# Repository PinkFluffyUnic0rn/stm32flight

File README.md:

STM32 Flight controller
=========================

DIY quadcopter flight controller from scratch, two boards and software.

[Project structure](https://github.com/PinkFluffyUnic0rn/stm32flight/wiki/Project-structure) 
is described on wiki page.

Software
=======

Software part implements all basic quadcopter flight control features.
Configuration commands and settings are on
[wiki page](https://github.com/PinkFluffyUnic0rn/stm32flight/wiki/FC-configuration-commands-and-settings).

* Rotation speed stabilization using gyroscope readings.
* Attitude stabilization using accelerometer/gyroscope readings.
* Yaw stabilization using gyroscope readings.
* Yaw stabilization using magnetometer/gyroscope readings.
* Acceleration stabilization using accelerometer readings.
* Altitude stabilization using barometer/accelerometer readings.
* Position stabilization using GNSS/accelerometer/magnetometer readings.
* Configuration through Wi-Fi.
* Dshot-300 and Dshot-600 ESC control protocols.
* IRC Tramp VTX control.
* OSD for digital VTX through MSP.
* Telemetry and control through eLRS.
* Terminal configuration tool.
* Qt5 based GUI configuration tool for desktop and android.

STM32H723 based board
=======
[Schematic](https://github.com/PinkFluffyUnic0rn/stm32flight/blob/main/pcb/H7/schematic.pdf)

 * MCU: STM32H723VGT6
 * Crystall oscillator: 20 Mhz
 * DC-DC converter for control board: TPS5430
 * Control board voltage regulator: LDL1117S33R
 * Accelerometer/Gyroscope: ICM-42688-P
 * Barometer: DPS368
 * Magnetometer: LIS3MDL
 * External magnetometer: MMC5983MA
 * Flight log storage: W25Q
 * GNSS module: M10
 * Remote control: ERLS CRSF receiver
 * Telemetry/debug/config: ESP8285

STM32F405 based board
=======
 * MCU: STM32F405RGT6
 * Crystall oscillator: 20 Mhz
 * DC-DC converter for control board: TPS5430 (external)
 * Control board voltage regulator: LDL1117S33R-3.3
 * Accelerometer/Gyroscope: ICM-42688-P
 * Barometer: DPS368
 * Magnetometer: QMC5883L
 * Flight log storage: W25Q
 * GNSS module: M10
 * Remote control: ERLS CRSF receiver
 * Telemetry/debug/config: ESP8285

The quadcopter used for testing
==========
 * Motors: 1404, 3800 kV
 * Props: 3030
 * Battery: 14.8v (4s), 1300 mAh, 120c
 * Frame: carbon fiber
 * Canopy, VTX mount: 3d printed PLA
 * Landing pads: EVA foam

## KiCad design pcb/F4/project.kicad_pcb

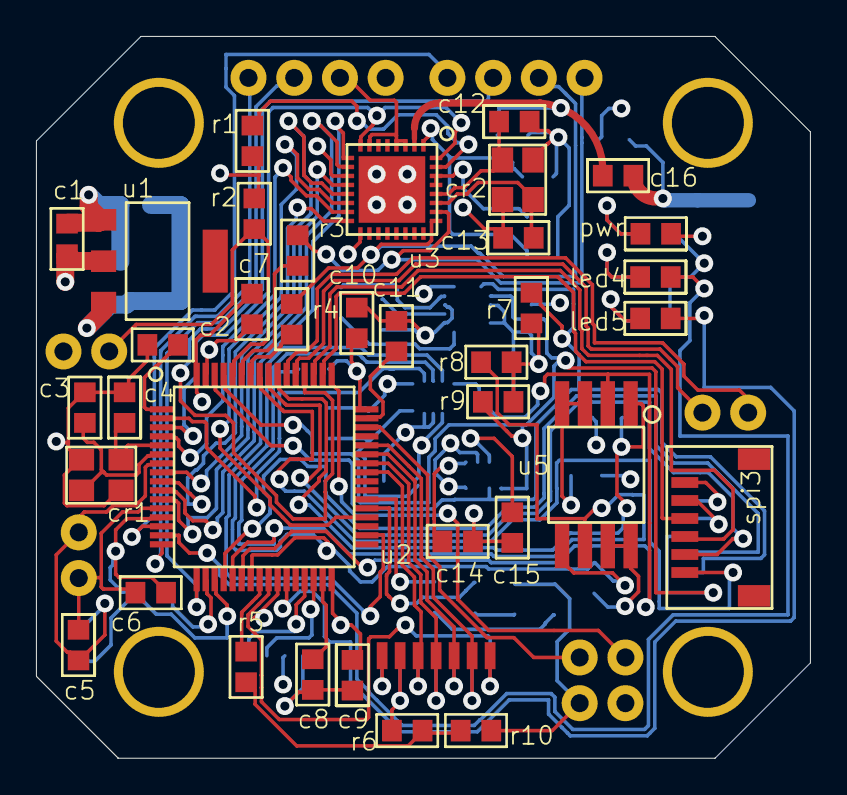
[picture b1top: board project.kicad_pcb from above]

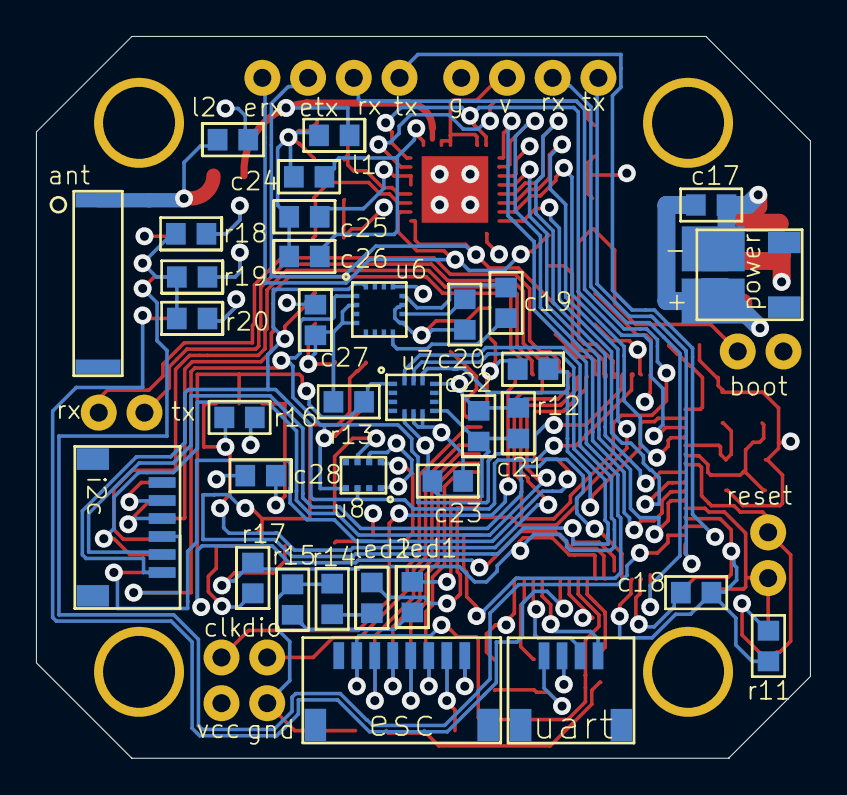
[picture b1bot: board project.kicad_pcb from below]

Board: 4 copper layers, 43.0 x 40.1 mm, 70 parts (34 on the bottom side), 45 nets.

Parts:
ant: Comment; rainsun antenna
c1: Comment; PCBComponent_1
c2, c3, c4, c5, c6, c7, c8, c9, c10, c11, c12, c13, c14, c15, c16, c17, c18, c19, c20, c21, c22, c23, c24, c25, c26, c27, c28: Comment; 0603
cr1, cr2: Comment; smd_crystall
esc: Comment; SH1.0-8
i2c: Comment; SH1.0-6
l1, l2: Comment; 0603
led1, led2, led4, led5: Comment; 0603
power: Comment; sh1.0-2
pwr: Comment; 0603
r1, r2, r3, r4, r5, r6, r7, r8, r9, r10, r11, r12, r13, r14, r15, r16, r17, r18, r19, r20: Comment; 0603
spi3: Comment; SH1.0-6
u1: Comment; ams1117
u2: Comment; lqfp64
u3: Comment; esp8285
u5: Comment; w25q
u6: Comment; qmc5883l
u7: Comment; icm42688
u8: Comment; DPS368
uart: Comment; sh1.0-4

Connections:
ant: ant.6, c16.1, l2.1
antcap: c16.1, l1.1, u3.4
boot: r2.1, u2.1
ch1: esc.1, u2.1
ch2: esc.1, u2.1
ch3: esc.1, u2.1
ch4: esc.1, u2.1
ch5: spi3.1, u2.1
ch6: spi3.1, u2.1
cs1: r12.1, u2.1, u7.1
cs2: r16.1, u2.1, u5.1
cs4: u2.1, u3.4
current: esc.1, u2.1
esp_rx: r3.1, u3.4
esp_tx: r4.1, u3.4
espboot: u2.1, u3.4
ext_rstb: u2.1, u3.4
exti1: u2.1, u3.4
gnd: c1.1, c2.1, c3.1, c4.1, c5.1, c6.1, c7.1, c8.1, c9.1, c10.1, c11.1, c12.1, c13.1, c14.1, c15.1, c17.1, c18.1, c20.1, c21.1, c22.1, c23.1, c24.1, c25.1, c26.1, c27.1, c28.1, cr1.3, cr2.3, esc.1, i2c.1, l1.1, l2.1, power.1, r1.1, r2.1, r10.1, r14.1, r15.1, r18.1, r19.1, r20.1, spi3.1, u1.1, u2.1, u5.1, u6.1, u7.1, u8.1, uart.1
led1: led2.1, u2.1
led1r: led2.1, r14.1
led2: led1.1, u2.1
led2r: led1.1, r15.1
led3r: pwr.1, r18.1
led4: led4.1, u2.1
led4r: led4.1, r19.1
led5: led5.1, u2.1
led5r: led5.1, r20.1
miso: r13.1, u2.1, u5.1, u7.1
miso2: u2.1, u3.4
mosi: r17.1, u2.1, u5.1, u7.1
mosi2: u2.1, u3.4
nrst: c5.1, r11.1, u2.1
osc_in: c4.1, cr1.3, u2.1
osc_out: c3.1, cr1.3, u2.1
pa4: i2c.1, u2.1
pa15: spi3.1, u2.1
pb15: u2.1, u3.4
pc10: spi3.1, u2.1
qmc_c1: c20.1, u6.1
qmc_setc: c19.1, u6.1
qmc_setp: c19.1, u6.1
res12k: r1.1, u3.4
rx1: r3.1, u2.1
rx3: u2.1, uart.1
sck: r8.1, u2.1, u5.1, u7.1
sck2: u2.1, u3.4
scl: i2c.1, r9.1, u2.1, u6.1, u8.1
sda: i2c.1, r7.1, u2.1, u6.1, u8.1
tx1: r4.1, u2.1
tx3: u2.1, uart.1
v2_1: r5.1, r6.1, r10.1
v2_2: r5.1, u2.1
vbat: c2.1, u2.1
vcap1: c8.1, u2.1
vcap2: c11.1, u2.1
vcc: c1.1, c6.1, c7.1, c9.1, c10.1, c14.1, c15.1, c18.1, c21.1, c22.1, c23.1, c24.1, c25.1, c26.1, c27.1, c28.1, i2c.1, pwr.1, r7.1, r8.1, r9.1, r11.1, r12.1, r13.1, r16.1, r17.1, spi3.1, u1.1, u2.1, u3.4, u5.1, u6.1, u7.1, u8.1, uart.1
vesc: esc.1, r6.1
vin: c17.1, power.1, u1.1
xtal_in: c12.1, cr2.3, u3.4
xtal_out: c13.1, cr2.3, u3.4

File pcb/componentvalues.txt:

c1	4.7 uF
c2	0.1 uF
c3	18 pF
c4	18 pF
c5	0.1 uF
c6	0.01 uF
c7	0.1 uF
c8	2.2 uF
c9	0.1 uF
c10	0.1 uF
c11	2.2 uF
c12	18 pF
c13	18 pF
c14	0.1 uF
c15	0.1 uF
c16	5.6 pF
c17	1 uF
c18	0.1 uF
c19	0.22 uF
c20	4.7 uF
c21	2.2 uF
c22	0.1 uF
c23	0.01 uF
c24	0.01 uF
c25	0.1 uF
c26	1 uF
c27	0.1 uF
c28	0.1 uF

r1	12k
r2	10k
r3	-
r4	-
r5	0 Ohm
r6	3k
r7	10k
r8	10k
r9	10k
r10	680 Ohm
r11	10k
r12	10k
r13	10k
r14	1k
r15	1k
r16	10k
r17	10k
r18	1k
r19	1k
r20	1k

l1	-
l2	-

cr1	20 mHz
cr2	40 mHz
led1	orange led
led2	blue led
pwr	green led
led4	yellow led
led5	red led

u1	LDL1117S33R
u2	STM32F405RGT6
u3	ESP8285
u4	DPS368
u5	W25Q128FVSIG
u6	QMC5883L
u7	ICM-42688-P

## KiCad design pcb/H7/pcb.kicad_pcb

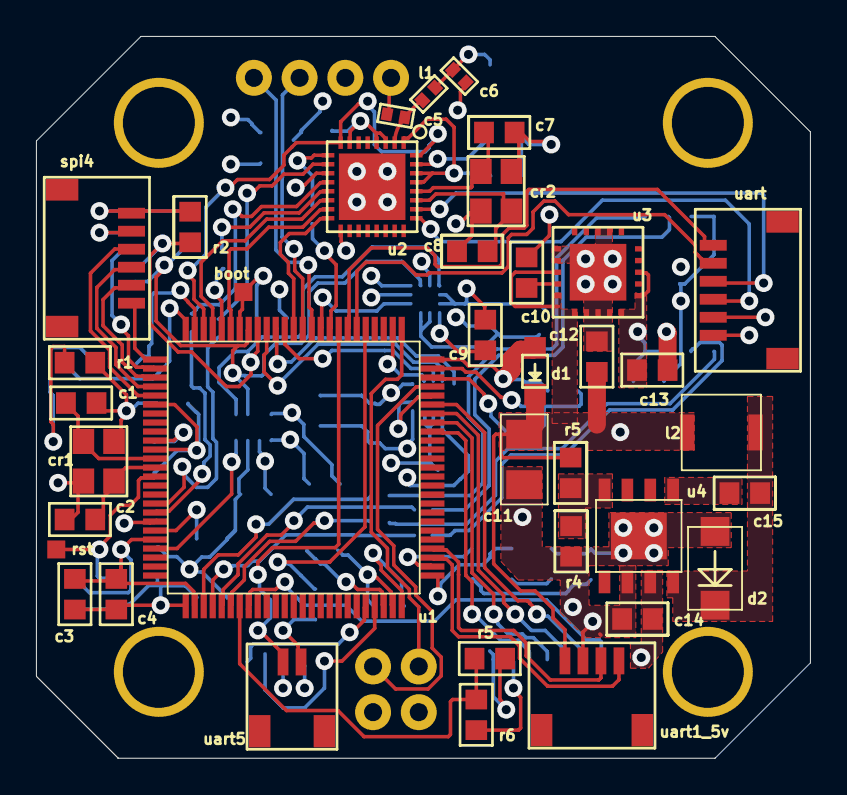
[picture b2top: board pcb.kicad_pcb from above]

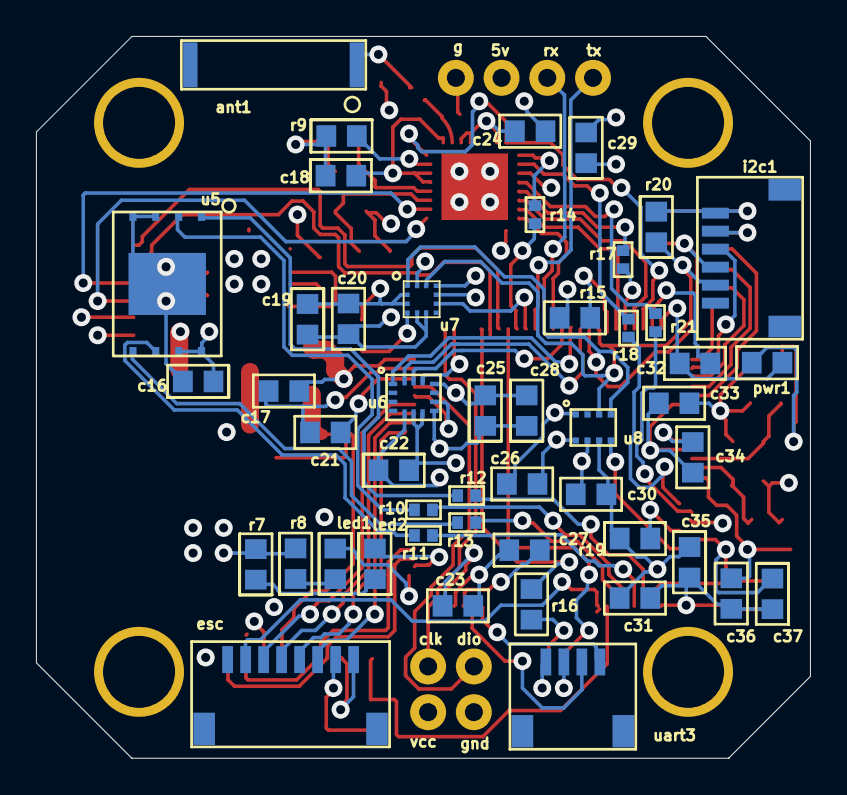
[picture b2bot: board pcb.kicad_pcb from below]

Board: 4 copper layers, 43.0 x 40.1 mm, 83 parts (48 on the bottom side), 59 nets.

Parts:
ant1: AN9520; rainsun antenna
c1, c2, c7, c8: 18 pF; 0603
c3, c10, c18, c20, c35: 1 uF; 0603
c4, c9, c16, c17, c19, c23, c24, c25, c26, c30, c31, c32, c33, c34, c36, c37: 0.1 uF; 0603
c5, c6: tbd; 0402
c11: 100 uF; 1206
c12, c14, c29: 10 uF; 0603
c13: 47 uF; 0603
c15, c22: 0.01 uF; 0603
c21, c27, c28: 2.2 uF; 0603
cr1: 20 Mhz; smd_crystall
cr2: 40 Mhz; smd_crystall
d1: Comment; SOD-323
d2: SS34
esc: JST SH-8; SH1.0-8
i2c1: JST SH-6; SH1.0-6
l1: tdb; 0402
l2: 10 uH; inductor
led1: blue LED; 0603
led2: orange LED; 0603
pwr1: green LED; 0603
r1, r7, r8: 1 kOhm; 0603
r2, r20: 3 kOhm; 0603
r4: 3.3 kOhm; 0603
r5: 680 Ohm; 0603
r5#2, r15: 10 kOhm; 0603
r6: 5.1 kOhm; 0603
r9: 12 kOhm; 0603
r10, r11, r12, r13, r14, r17, r18, r21: 33 Ohm; 0402
r16: 100 Ohm; 0603
r19: 47 Ohm; 0603
spi4: JST SH-6; SH1.0-6
u1: STMH723VGT6; lqfp100
u2: ESP8285; esp8285
u3: TPS7A4700; TPS7A470
u4: TPS5430DDAR; tps5430
u5: Comment; W25N
u6: ICM-42688-P; icm42688
u7: LIS3MDLTR; lis3mdl
u8: DPS368XTSA1; DPS368
uart: JST SH-6; SH1.0-6
uart1_5v, uart3: JST SH-4; sh1.0-4
uart5: JST SH-2; sh1.0-2

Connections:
ant: ant1.6, c6.1, l1.1
antcap: c5.1, l1.1, u2.4
boot: r15.1, u1.1
ch1: esc.1, u1.1
ch2: esc.1, u1.1
ch3: esc.1, u1.1
ch4: esc.1, u1.1
current: esc.1, u1.1
dcdc_boot: c15.1, u4.9
drdy: u1.1, u7.6
esp_rx: u2.4, uart.1
esp_tx: u2.4, uart.1
espboot: u1.1, u2.4
ext_rstb: u1.1, u2.4
exti1: u1.1, u2.4
fsync: u1.1, u6.1
gnd: c1.1, c2.1, c3.1, c4.1, c5.1, c6.1, c7.1, c8.1, c9.1, c10.1, c11.10, c12.1, c13.1, c14.1, c16.1, c17.1, c18.1, c19.1, c20.1, c21.1, c22.1, c23.1, c24.1, c25.1, c26.1, c27.1, c28.1, c29.1, c30.1, c31.1, c32.1, c33.1, c34.1, c35.1, c36.1, c37.1, cr1.3, cr2.3, d2.8, esc.1, i2c1.1, r1.1, r4.1, r5.1, r7.1, r8.1, r9.1, r15.1, spi4.1, u1.1, u3.9, u3.10, u4.9, u5.11, u5.12, u6.1, u7.6, u8.1, uart.1, uart1_5v.1, uart3.1
led1: led1.1, u1.1
led1r: led1.1, r8.1
led2: led2.1, u1.1
led2r: led2.1, r7.1
lis_c1: c9.1, u7.6
loop: c15.1, d2.8, l2.7, u4.9
miso1_1: r10.1, u1.1
miso1_2: r10.1, u5.12
miso2_1: r18.1, u1.1
miso2_2: r18.1, u2.4
miso3: u1.1, u6.1
miso4: spi4.1, u1.1
mosi1_1: r13.1, u1.1
mosi1_2: r13.1, u5.12
mosi2_1: r21.1, u1.1
mosi2_2: r21.1, u2.4
mosi3: u1.1, u6.1
mosi4: spi4.1, u1.1
nr: c10.1, u3.9
nrst: c36.1, u1.1
nss1_1: r12.1, u1.1
nss1_2: r12.1, u5.12
nss2_1: r17.1, u1.1
nss2_2: r17.1, u2.4
nss3: u1.1, u6.1
nss4: spi4.1, u1.1
osc_in: c1.1, cr1.3, u1.1
osc_out: c2.1, cr1.3, u1.1
pe0: u1.1, u2.4
pe3: i2c1.1, u1.1
pwrled: pwr1.1, r1.1
res12k: r9.1, u2.4
rx1: u1.1, uart1_5v.1
rx3: u1.1, uart3.1
rx4: u1.1, uart.1
rx5: u1.1, uart5.1
sck1_1: r11.1, u1.1
sck1_2: r11.1, u5.12
sck2_1: r14.1, u1.1
sck2_2: r14.1, u2.4
sck3: u1.1, u6.1
sck4: spi4.1, u1.1
scl: i2c1.1, r2.1, u1.1, u7.6, u8.1
sda: i2c1.1, r20.1, u1.1, u7.6, u8.1
sdo: u1.1, u8.1
sence: r4.1, r5#2.1, u4.9
tx1: u1.1, uart1_5v.1
tx3: u1.1, uart3.1
tx4: u1.1, uart.1
tx5_1: r16.1, u1.1
tx5_2: r16.1, uart5.1
v5: c11.10, c12.1, d1.4, l2.7, r5#2.1, u3.9, uart1_5v.1
v_bat: r5.1, r6.1, u1.1
vcap1: c21.1, u1.1
vcap2: c27.1, u1.1
vcc: c3.1, c4.1, c13.1, c16.1, c17.1, c18.1, c19.1, c20.1, c22.1, c23.1, c24.1, c25.1, c26.1, c28.1, c29.1, c30.1, c31.1, c32.1, c33.1, c34.1, c35.1, c37.1, d1.4, i2c1.1, pwr1.1, r2.1, r19.1, r20.1, spi4.1, u1.1, u2.4, u3.9, u5.12, u6.1, u7.6, u8.1, uart.1, uart3.1
vin: c14.1, esc.1, r6.1, u4.9
vref+: r19.1, u1.1
xtal_in: c7.1, cr2.3, u2.4
xtal_out: c8.1, cr2.3, u2.4

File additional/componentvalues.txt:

main board:
c1	0.1 uF
c2	0.1 uF
c3	18 pF
c4	18 pF
c5	0.1 uF
c6	0.1 uF
c9	0.1 uF
c11	2.2 uF
c12	0.1 uF
c13	0.1 uF
c14	2.2 uF
c15	5.6 pF
l1	18 pF
c16	18 pF
c17	0.1 uF
c18	10 uF
c19	0.1 uF
c20	0.22 uF
c21	4.7 uF
c22	0.1 uF
c23	2.2 uF
c24	0.01 uF
c26	0.1 uF
c27	0.1 uF
c28	0.1 uF
c29	0.1 uF
c31	0.1 uF

c7	12 kOhm
c8	0 Ohm
c30	10 kOhm
c10	0 Ohm
r1	10k
r2	3 kOhm
r3	10 kOhm
r4	3 kOhm
r5	10 kOhm
r6	10 kOhm
r7	1k
r8	1k
r9	10k
r10	10k

c25	mH
l2	mH

led1:	orange led
led2:	blue led
u1:	AMS1117-3.3
u2:	STM32F405RGT6
u3:	ESP8285
u4:	HP206C
u5:	W25Q128FVSIG
u6:	ICM-42688-P
u7:	QMC5883L

dc-dc converter:
l1:	10 uH
r1:	10 kOhm
r2:	3.3 kOhm
r3:	4.7 kOhm
r4:	27 kOhm
c1:	0.1 uF
c2:	10 uF
c3:	100 uF
u1:	tps5430

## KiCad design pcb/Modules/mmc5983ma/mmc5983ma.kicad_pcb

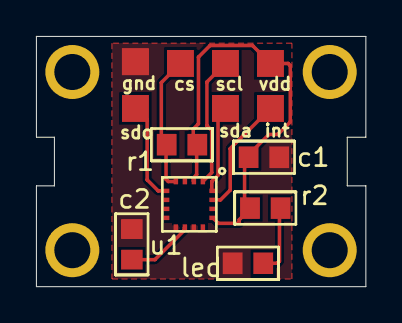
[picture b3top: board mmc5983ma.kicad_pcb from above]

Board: 2 copper layers, 18.3 x 13.9 mm, 6 parts (0 on the bottom side), 5 nets.

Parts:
c1, c2: Comment; 0603
led: Comment; 0603
r1, r2: Comment; 0603
u1: Comment; qmc5883l

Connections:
cap: c2.1, u1.1
cs: r1.1, u1.1
gnd: c1.1, c2.1, led.1, u1.1
led: led.1, r2.1
vcc: c1.1, r1.1, r2.1, u1.1

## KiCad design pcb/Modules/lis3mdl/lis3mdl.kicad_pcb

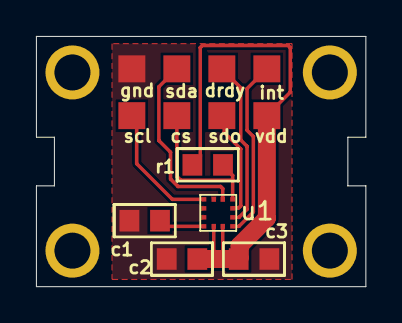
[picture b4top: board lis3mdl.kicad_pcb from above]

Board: 2 copper layers, 18.3 x 13.9 mm, 5 parts (0 on the bottom side), 4 nets.

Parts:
c1, c2, c3: Comment; 0603
r1: Comment; 0603
u1: Comment; lis3mdl

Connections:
c1: c1.1, u1.6
cs: r1.1, u1.6
gnd: c1.1, c2.1, c3.1, u1.6
vdd: c2.1, c3.1, r1.1, u1.6

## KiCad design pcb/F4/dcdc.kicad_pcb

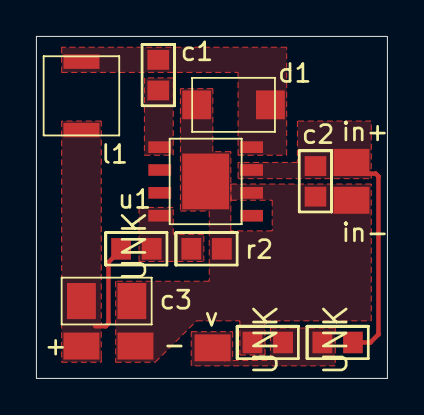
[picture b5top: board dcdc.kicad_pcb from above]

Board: 2 copper layers, 19.5 x 19.0 mm, 10 parts (0 on the bottom side), 7 nets.

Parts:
UNK: Comment; 0603
UNK#2, UNK#3: Comment; 0603
c1, c2: Comment; 0603
c3: Comment; 1206
d1: Comment; SS34
l1: Comment; inductor
r2: Comment; 0603
u1: Comment; tps5430

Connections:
boot: c1.1, u1.9
gnd: UNK#3.1, c2.1, c3.10, d1.8, r2.1, u1.9
in: UNK.1, c2.1, u1.9
loop: c1.1, d1.8, l1.7, u1.9
out: UNK#2.1, c3.10, l1.7
sense: UNK#2.1, r2.1, u1.9
v: UNK.1, UNK#3.1

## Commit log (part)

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2024-10-30 circuit updated
2024-10-30 dc-dc circuit added
2024-10-30 dc-dc circuit fix
2024-10-30 dc-dc converted info updated
2024-11-03 Debug conenction is now made by AP created by copter
2024-11-03 README.md changed
2024-11-03 README.md fixed
2024-11-08 README updated
2024-11-14 yaw control is now performed by left joystick
2024-11-14 wifi timeut removed, wifi control commands removed
2024-11-14 rc cleanup
2024-11-16 README.md update
2024-11-19 Some main.c comments added
2024-11-19 main.c comments updated
2024-11-20 dsp comments updated
2024-11-20 README.md update, comments update
2024-11-23 trying to add climb with constant rate by barometer
2024-11-23 trying to use barometer
2024-11-24 altitude reset from elrs
2024-11-24 arming indication and error leds added
2024-11-26 onboard flash activated
2024-11-26 trying to estimate climb rate from accelerometer
2024-12-02 trying to make constant climb speed
2024-12-02 config change
2024-12-05 gyro calibration on start removed
2024-12-05 tilt is now limited with 45 degrees instead of 30
2024-12-05 some cleanup, comments updated
2024-12-23 switched to new board, with mpu6500
2025-02-23 Starting without esp8266 restart
2025-02-25 Tried to fix baudrate on-run change for esp8266, removed hardcoded mpu6500 offsets
2025-02-25 SPI baudrate divider set to 4, some cleanup
2025-02-25 flash log fixes, log set size commands added
2025-02-26 add new values to log
2025-02-26 event timer remain added
2025-02-26 using remain to adjust frequency
2025-02-27 fixed w25q timeouts, esp8266 baudrate slowed
2025-02-28 esp8266 memmove removed from callback
2025-03-01 PLL multiplier increased, enqueqe function for ESP8266 fifo removed
2025-03-06 GNSS added
2025-03-08 ESP8266 switched to same interface as other devices
2025-03-08 debug commands refactored
2025-03-09 Device status command added
2025-03-09 Added comment
2025-03-09 Telemetry fixes and refactoring
2025-03-10 altitude telemetry fix
2025-03-17 vertical speed calculation by vector projection added
2025-03-17 altitude complimentary filter added
2025-03-20 MPU6500 dlpf changes
2025-03-22 Yaw complimentary filter added to merge magnetometer heading and gyro z axis
2025-03-22 Create LICENSE
2025-03-23 Some naming fixes
2025-03-23 Motor thrust adjust added
2025-04-08 Switched to stm32f405 and ICM42688
2025-04-08 README fixed
2025-04-11 motors changed
2025-04-17 values changed; unused values list deleted
2025-04-17 values updated
2025-04-17 more accurate weights measured
2025-04-17 compopnent values updated
2025-04-20 comment removed
2025-04-21 switched to multishot
2025-05-05 switched to new board with esp connected through SPI
2025-05-05 esp32 code added
2025-05-05 values changed
2025-05-06 Board changed
2025-05-08 switched to all-in-one esc, pid frequency set to 4k
2025-05-08 README changed
2025-05-09 pitch correction removed
2025-05-14 Fixing wifi connection for high speed upload
2025-05-15 Reworking confuration commands protocol
2025-05-16 trying to speed up spi
2025-05-16 changed UDP packet size
2025-05-18 trying to get better spi transmition speed
2025-05-19 log transmition protocol enhanced
2025-05-20 small README error fixed
2025-05-20 spaces removed, uavconf comments added
2025-05-20 sub microsecond delays added
2025-05-20 util comments added
2025-05-21 log record size changed
2025-05-21 maximum thrust value added
2025-05-22 spi speed lowered
2025-05-22 write only mode for w25q added
2025-05-22 emergency disarm when upside down, ESP SPI CRC check disabled
2025-05-23 disabled magnetometer check, values adjusted
2025-05-23 README.md updated with log documentation
2025-05-23 switched to CRC-16 for controll comamnds and log records, stm32 periphery initialization moved to separate file
2025-05-24 PT1 filter added
2025-05-24 trying to fix drifting
2025-05-29 esp8266 bugfixes, acro mode returned
2025-06-01 magnetometer OSR increased
2025-06-05 gyro lpf added, PID values changed
2025-06-06 D term filtering added
2025-06-07 pid changes
2025-06-09 voltage monitoring added
2025-06-09 pcb directory renamed
2025-06-09 battery monitoring divider changed, battery monitor lpf added
2025-06-09 component values updated
2025-06-12 config generation gui tool added
2025-06-12 working on config gui
2025-06-12 commands added to gui widgets
2025-06-13 commands parsing to common structure added
2025-06-14 Info tab added
2025-06-14 hotkeys added`
2025-06-14 classes refactoring
2025-06-17 uav command check fixed
2025-06-24 terminal uavconf connected to same API
2025-06-24 directory structure changed
2025-06-24 uavconf directory structure reworking
2025-06-28 frame changed, crsf channels enum added
2025-07-03 swtiched to dshot
2025-07-03 dshot cosmetic changes
2025-07-04 README updated, dshot comments added
2025-07-06 delays changed, ESCs configuration added
2025-07-10 partial setting send added, trying to altitude hold make stabilize when moving
2025-07-13 PID tuning for 2s battery set using Ziegler-Nichols method, I-term computing disabled disarmed
2025-07-15 No I-term when no throttle
2025-07-16 trying to setup thrust PIDs
2025-07-27 log field mapping fixes
2025-07-27 log writing fixes
2025-07-28 working on log guia config
2025-07-29 working on log config
2025-07-29 unique record field indexes in gui added
2025-07-31 log writing fix for maximum records count, w25 timeouts bugfix, stm32 systick to float seconds utility function added
2025-07-31 Log functions and settings moved to separate files
2025-08-01 log downloading cmd priniting to terminal added, get log record command timeout increased
2025-08-06 pcb updated, sensor adjustments changed
2025-08-10 4s pid values adjusted
2025-09-08 switching to dps368, working on stable altitude hold
2025-09-10 trying to work with hover throttle
2025-09-10 new pcb added
2025-09-12 stabilized around hover throttle acceleration mode added, altitude hold around hover throttle added
2025-09-14 hover throttle tilt compensation fixed
2025-09-15 clear i term when zero throttle
2025-10-01 hover throttle tilt compensation changed
2025-10-05 This is BOM
    You can edit it according to your region but I have used mostly internationally available parts.
2025-10-05 This is CPL file
    I haven't referenced it at all, I will complete it later as I don't have time right now. All the footprints are same as given in Gerber files.
2025-10-14 althold fixes
2025-10-18 git accelerometer offset added
2025-11-06 i2c and uart tx processed through DMA, bilinear PID implementaion added
2025-11-06 trying to switch to bilinear transform derived PID
2025-11-08 bilinear transform derived PID I-term clamp and I-term reset added
2025-11-09 Doxygen for dsp.h added
2025-11-09 I-term limit adjusted
2025-11-09 Command, CRC, global and log doxygen added
2025-11-10 main.c doxygen added
2025-11-10 logging event enabled, set_pid return codes fixed
2025-11-10 cosmetic changes
2025-12-10 trying to fight altitude drop, custom log values added
2025-12-16 magnetometer thrust calibration added
2025-12-17 config commands, dshot and running values moved to separate files
2025-12-17 magnetometer calibrated better
2025-12-18 error accumulation when disarmed is fixed
2026-01-03 autopilot activation flag protection
2026-01-04 autopilot yaw added
2026-01-05 adding autopilot settings
2026-01-05 zero autopilot track points protection
2026-01-12 PCB added
2026-01-12 filters and pid controllers grouped into arrays
2026-01-13 Setting switched to nested structure
2026-01-13 global variable names now start with capital letters, magnetometer offset applied immideately
2026-01-13 tscale fixed
2026-01-14 roll, pitch, yaw offsets now calculated once, circular PID how using bilinear transform
2026-01-14 Separaty apply command added
2026-01-15 unified set command for all settings added
2026-02-02 DShot moved to separate device
2026-02-07 periphery initialization reworked
2026-02-08 added periphconf
2026-02-15 devices initialization reworked
2026-02-15 Log analyzing scripts pushed
2026-02-16 makefile reworked, stm32h7 hal added
2026-02-17 working on stm32h7 support
2026-02-20 trying to fix dshot for H7
2026-02-20 fixing adc for H7
2026-02-21 debug uart interrupt fixed
2026-02-22 trying to fix dshot issue on H7
2026-02-23 upadted readme
2026-02-24 Kicad project added for H7
2026-02-24 README.md updated again
2026-02-24 schematic updated
2026-02-24 schematic source updated
2026-02-24 pcb update
2026-02-24 F4 pcb updated
2026-02-24 schematic added to readme
2026-02-25 small comment fix
2026-02-25 schematic fix
2026-02-26 trying to fix dshot issue with high frequency timer, schematic numbers fix
2026-02-28 trying to fix dshot issue
2026-03-07 schematic upadted
2026-03-07 irc vtx inittialization fix
2026-03-07 irc fix
2026-03-09 current sence fix
2026-03-09 working on magnetometer calibration script
2026-03-10 battery sensor scaling added, i term scaling for dual loop pid mode added, configs updated
2026-03-10 adc sampling time changed
2026-03-10 adjusting adc
2026-03-10 calibration order change
2026-03-10 magnetometer config update for h7
2026-03-11 scheduler time measurement improved
2026-03-11 STM32F4 scheduler fix
2026-03-13 magnetometer calibration script frequnecy changed
2026-03-15 dma waiting before new transaction added
2026-03-18 STM32H7 swithced adc to dma, profiler added
2026-03-19 altitude complimentary filter update moved to main PID event
2026-03-20 dshot bit length from timer frequency calculation added, tilt compensation for altitude hold added
2026-03-23 dma burst mode for dshot added, adc oversampling enabled
2026-03-25 spi frequency raised to 24 mhz for H7, maximum log frequency raised to 8khz, accelerometer range raised to 16g, adjustments changed in config, dshot-600 adjustments added
2026-03-26 dshot timings put to constants
2026-03-27 adding msp osd
2026-03-28 MSP optimization, switched to DMA
2026-03-28 telemetry event one sprintf removed
2026-03-30 OSD fixes, tried to recalibrate magnetometer for digital vtx
2026-03-31 float to string fixes
2026-04-02 making F405 controller working again
2026-04-02 stm32f405 adc dma enabled, stm32h7 current meter adjustments
2026-04-04 configuration commands through uart added
2026-04-05 osd and gps fixes
2026-04-07 doxygen updated
2026-04-07 doxygen for devices updated
2026-04-08 various fixes, removing unused variables, names and types fixes, uptime added into MSP OSD, magnetic direction OSD fix
2026-04-09 doxygen updated, most constants moved to settings.h, device initializaiton struct type in init functions updated
2026-04-09 disabling magnetometer using modes and barometer using modes when corresponding sensor disabled
2026-04-10 event triggering now bound to PID frequency, accelerometer reading moved to separate event, log writing batch size changed to 128 bytes, trying to fix wifi log downloading
2026-04-14 empty command crc check fix, gui downloaded size output added, gnss log fields added
2026-04-14 barometric altitude thrust compensation added
2026-04-15 average throttle value added as log field
2026-04-17 barometric altitude speed correction added
2026-04-20 accelerometer euler angles and rotation matrix fix
2026-04-21 gyro calibration added, attitude complimentary filter time constant adjusted
2026-04-30 adding GNSS complimentary filter
2026-04-30 camera holder cad file added
2026-05-02 gnss speed control fix
2026-05-07 switched to lis3mdl for H7 board
2026-05-08 config update
2026-05-09 gps fixes
2026-05-09 gnss rotation fixes
2026-05-11 working on gps position hold
2026-05-12 gravity substraction added when projection acccelerometer readings
2026-05-16 4s config update
2026-05-18 stabilization loop moved to separate source file
2026-05-23 gpss control rates added
2026-05-25 swtiched to mmc5983ma
2026-05-27 mmc5983ma degaussing on every read, magnetometer recalibrated
2026-05-27 sensor data moved to separate file
2026-06-06 canopy updated
2026-06-06 switched mmc5983ma to 18 bit
2026-06-10 switched to new board with imu and w25q on separate SPIs
2026-06-13 lis3mdl int16_t to int32_t
2026-06-13 magnetometer for 4s recalibration
2026-06-18 trying to fix I-term accumulation
2026-06-20 thrust linearilation fix
2026-06-21 separate pin speed from different spi purposes
2026-06-23 log flash double buffering added, trying to fix dps368 data reading
